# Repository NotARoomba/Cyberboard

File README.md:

<h1 align="center">
  <br>
  
  <br>
  Cyberboard V2
  <br>
</h1>

<h4 align="center">
A Raspberry Pi Pico-sized STM32 development board with Bluetooth, battery support, IMU and a barometer!
</h4>

<div align="center">

</div>

<p align="center">
  <a href="#key-features">Key Features</a> •
  <a href="#pcb">PCB</a> •
  <a href="#credits">Credits</a> •
  <a href="#license">License</a>
</p>

> **⚠️ Looking for V1?** The first version of the Cyberboard is available in the [v1 branch](https://github.com/notaroomba/cyberboard/tree/v1), but be warned: it doesn't work. V2 is a complete redesign with proper functionality.

## Key Features

- **STM32WB55CG** microcontroller with Bluetooth support
- **Raspberry Pi Pico form factor** for compatibility
- **IMU and Barometer** - ICM-42688 (6-axis) and BMP580 pressure sensor for environmental/motion sensing
- **Battery charging** with BQ24072RGTR IC and solder pad for 1S LiPo
- **Buck-Boost converter** (TPS631000) for efficient power management
- **Multiple Status LEDs** for visual feedback
- **USB-C** connectivity
- **Ceramic Bluetooth antenna** with impedance matching
- **SWD test points** on the bottom for easy programming
- **4-layer PCB** design with optimized RF layout and routing
- **Panelized design** for cost-effective manufacturing

## PCB

Designed in KiCad with attention to RF design, power management, and sensor integration. The board features a 4-layer stackup (SIG/GND/PWR/SIG) with optimized routing for the Bluetooth antenna and sensitive analog signals.

### Schematic

### PCB Layers

The 4-layer stackup (SIG/GND/PWR/SIG) provides optimal signal integrity and power distribution:

**Layer 1 (Signal):**

**Layer 2 (Ground):**

**Layer 3 (Power):**

**Layer 4 (Signal):**

**Front:**

**Back:**

### JLCPCB Order

## Credits

This project uses:

- [KiCad](https://www.kicad.org/)
- [Blender](https://www.blender.org/) for 3D renders
- [Hack Club Blueprint](https://blueprint.hackclub.com/projects/491)

## You may also like...

- [CyberCard](https://github.com/NotARoomba/CyberCard) – A Cyberpunk themed NFC hacker card
- [Ember](https://github.com/NotARoomba/ember) – USB-C PD Powered Hotplate
- [Trace](https://github.com/NotARoomba/trace) – An ruler for engineers
- [Athena](https://github.com/NotARoomba/athena) – A flight controlelr with a triple MCU architecture

## License

MIT

---

> [notaroomba.dev](https://notaroomba.dev) &nbsp;&middot;&nbsp;
> GitHub [@NotARoomba](https://github.com/NotARoomba) &nbsp;&middot;&nbsp;

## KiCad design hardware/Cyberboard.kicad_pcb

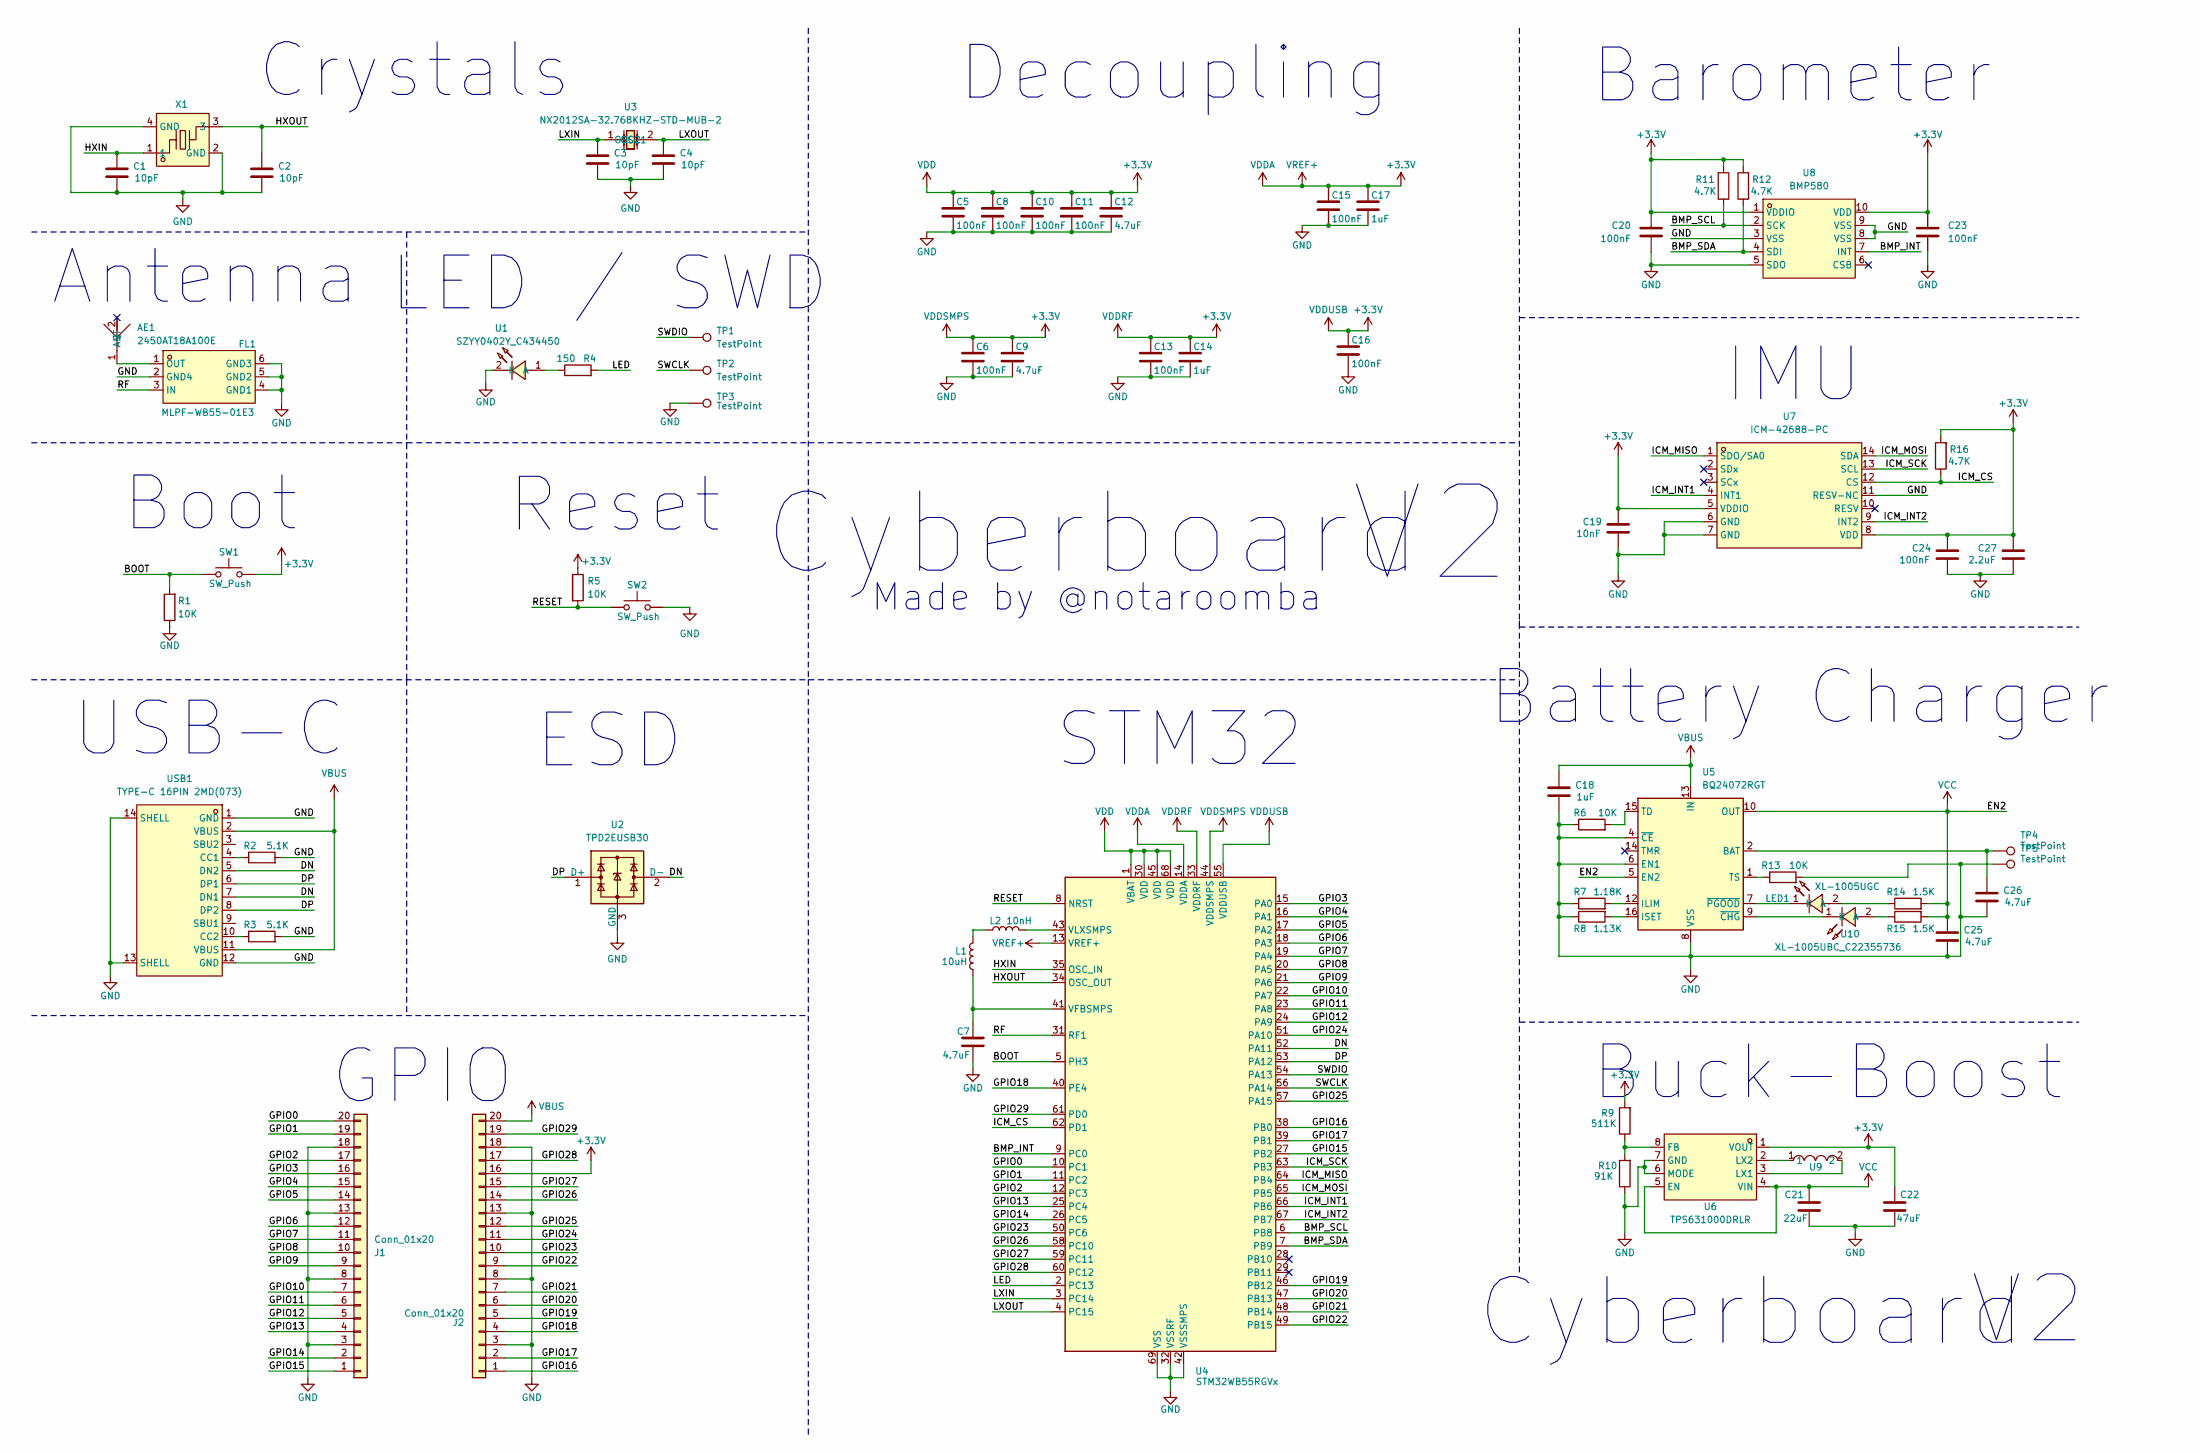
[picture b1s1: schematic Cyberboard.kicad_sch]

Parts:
AE1: 2450AT18A100E; ANT-SMD_L3.2-W1.6; LCSC Part C89334
C1, C2, C3, C4: 10pF; C_0402_1005Metric
C5, C6, C8, C10, C11, C13, C15, C16, C20, C23, C24: 100nF; C_0402_1005Metric
C7, C9, C12, C25, C26: 4.7uF; C_0603_1608Metric
C14, C17, C18: 1uF; C_0402_1005Metric
C19: 10nF; C_0402_1005Metric
C21: 22uF; C_0603_1608Metric; LCSC C361061
C22: 47uF; C_0805_2012Metric; LCSC C471380
C27: 2.2uF; C_0402_1005Metric
FL1: MLPF-WB55-01E3; FILTER-SMD_6P-L1.6-W1.0-P0.50-BL; LCSC Part C2651048
J1, J2: Conn_01x20; PinHeader_1x20_P2.54mm_Vertical; LCSC C42431804
L1: 10uH; L_0603_1608Metric
L2: 10nH; L_0603_1608Metric
LED1: XL-1005UGC; LED0402-RD_GREEN; LCSC Part C965793
R1, R5, R6, R13: 10K; R_0402_1005Metric
R2, R3: 5.1K; R_0402_1005Metric
R4: 150; R_0402_1005Metric; LCSC C25082
R7: 1.18K; R_0402_1005Metric
R8: 1.13K; R_0402_1005Metric
R9: 511K; R_0402_1005Metric
R10: 91K; R_0402_1005Metric
R11, R12, R16: 4.7K; R_0402_1005Metric
R14, R15: 1.5K; R_0402_1005Metric
SW1, SW2: SW_Push; SW-SMD_L3.9-W3.0-P4.45; LCSC C720477
TP1, TP2, TP3: TestPoint; TestPoint_Pad_1.0x1.0mm
TP4, TP5: TestPoint; TestPoint_Pad_2.0x2.0mm
U1: SZYY0402Y_C434450; LED0402-FD_YELLOW; LCSC Part C434450
U2: TPD2EUSB30; Texas_DRT-3
U3: NX2012SA-32.768KHZ-STD-MUB-2; CRYSTAL-SMD_L2.0-W1.2; LCSC Part C891748
U4: STM32WB55RGVx; QFN-68-1EP_8x8mm_P0.4mm_EP6.4x6.4mm; LCSC C401505
U5: BQ24072RGT; VQFN-16-1EP_3x3mm_P0.5mm_EP1.6x1.6mm; LCSC C140288
U6: TPS631000DRLR; SOT-583-8_L2.1-W1.2-P0.50-LS1.6-BL; LCSC Part C5219190
U7: ICM-42688-PC; LGA-14_L3.0-W2.5-P0.50-TL; LCSC Part C48586483
U8: BMP580; LGA-10_L2.0-W2.0-P0.50-TL_BMP580; LCSC Part C22391138
U9: DFE252012P-1R0M=P2; L1008; LCSC Part C882955
U10: XL-1005UBC_C22355736; LED0402-RD; LCSC Part C22355736
USB1: TYPE-C 16PIN 2MD(073); USB-C-SMD_TYPE-C-6PIN-2MD-073; LCSC Part C2765186
X1: NX2016SA-32MHZ-STD-CZS-5; OSC-SMD_4P-L2.0-W1.6-BL; LCSC Part C843260

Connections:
+3.3V: C5.1, C6.1, C8.1, C9.1, C10.1, C11.1, C12.1, C13.1, C14.1, C15.1, C16.1, C17.1, C19.1, C20.1, C22.1, C23.1, C24.1, C27.1, J2.16, R5.1, R9.2, R11.2, R12.2, R16.2, SW1.2, U4.1 (VBAT), U4.13 (VREF+), U4.14 (VDDA), U4.30 (VDD), U4.33 (VDDRF), U4.44 (VDDSMPS), U4.45 (VDD), U4.55 (VDDUSB), U4.68 (VDD), U6.1 (VOUT), U7.5 (VDDIO), U7.8 (VDD), U8.1 (VDDIO), U8.10 (VDD)
/BMP_INT: U4.9 (PC0), U8.7 (INT)
/BMP_SCL: R11.1, U4.6 (PB8), U8.2 (SCK)
/BMP_SDA: R12.1, U4.7 (PB9), U8.4 (SDI)
/BOOT: R1.2, SW1.1, U4.5 (PH3)
/DN: U2.2 (D-), U4.52 (PA11), USB1.5 (DN2), USB1.7 (DN1)
/DP: U2.1 (D+), U4.53 (PA12), USB1.6 (DP1), USB1.8 (DP2)
/GPIO0: J1.20, U4.10 (PC1)
/GPIO1: J1.19, U4.11 (PC2)
/GPIO2: J1.17, U4.12 (PC3)
/GPIO3: J1.16, U4.15 (PA0)
/GPIO4: J1.15, U4.16 (PA1)
/GPIO5: J1.14, U4.17 (PA2)
/GPIO6: J1.12, U4.18 (PA3)
/GPIO7: J1.11, U4.19 (PA4)
/GPIO8: J1.10, U4.20 (PA5)
/GPIO9: J1.9, U4.21 (PA6)
/GPIO10: J1.7, U4.22 (PA7)
/GPIO11: J1.6, U4.23 (PA8)
/GPIO12: J1.5, U4.24 (PA9)
/GPIO13: J1.4, U4.25 (PC4)
/GPIO14: J1.2, U4.26 (PC5)
/GPIO15: J1.1, U4.27 (PB2)
/GPIO16: J2.1, U4.38 (PB0)
/GPIO17: J2.2, U4.39 (PB1)
/GPIO18: J2.4, U4.40 (PE4)
/GPIO19: J2.5, U4.46 (PB12)
/GPIO20: J2.6, U4.47 (PB13)
/GPIO21: J2.7, U4.48 (PB14)
/GPIO22: J2.9, U4.49 (PB15)
/GPIO23: J2.10, U4.50 (PC6)
/GPIO24: J2.11, U4.51 (PA10)
/GPIO25: J2.12, U4.57 (PA15)
/GPIO26: J2.14, U4.58 (PC10)
/GPIO27: J2.15, U4.59 (PC11)
/GPIO28: J2.17, U4.60 (PC12)
/GPIO29: J2.19, U4.61 (PD0)
/HXIN: C1.1, U4.35 (OSC_IN), X1.1
/HXOUT: C2.1, U4.34 (OSC_OUT), X1.3
/ICM_CS: R16.1, U4.62 (PD1), U7.12 (CS)
/ICM_INT1: U4.66 (PB6), U7.4 (INT1)
/ICM_INT2: U4.67 (PB7), U7.9 (INT2)
/ICM_MISO: U4.64 (PB4), U7.1 (SDO/SA0)
/ICM_MOSI: U4.65 (PB5), U7.14 (SDA)
/ICM_SCK: U4.63 (PB3), U7.13 (SCL)
/LED: R4.2, U4.2 (PC13)
/LXIN: C3.1, U3.1 (OSC1), U4.3 (PC14)
/LXOUT: C4.1, U3.2 (OSC2), U4.4 (PC15)
/RESET: R5.2, SW2.1, U4.8 (NRST)
/RF: FL1.3 (IN), U4.31 (RF1)
/SWCLK: TP2.1, U4.56 (PA14)
/SWDIO: TP1.1, U4.54 (PA13)
GND: C1.2, C2.2, C3.2, C4.2, C5.2, C6.2, C7.2, C8.2, C9.2, C10.2, C11.2, C12.2, C13.2, C14.2, C15.2, C16.2, C17.2, C18.2, C19.2, C20.2, C21.2, C22.2, C23.2, C24.2, C25.2, C26.2, C27.2, FL1.2 (GND4), FL1.4 (GND1), FL1.5 (GND2), FL1.6 (GND3), J1.3, J1.8, J1.13, J1.18, J2.3, J2.8, J2.13, J2.18, R1.1, R2.2, R3.2, R6.1, R7.1, R8.1, R10.1, R13.2, SW2.2, TP3.1, TP5.1, U1.2 (K), U2.3 (GND), U4.32 (VSSRF), U4.42 (VSSSMPS), U4.69 (VSS), U5.4 (~CE), U5.6 (EN1), U5.8 (VSS), U5.17 (VSS), U6.6 (MODE), U6.7 (GND), U7.6 (GND), U7.7 (GND), U7.11 (RESV-NC), U8.3 (VSS), U8.5 (SDO), U8.8 (VSS), U8.9 (VSS), USB1.1 (GND), USB1.12 (GND), USB1.13 (SHELL), USB1.14 (SHELL), X1.2 (GND), X1.4 (GND)
unnamed: AE1.1 (ANT), FL1.1 (OUT)
unnamed: C26.1, TP4.1, U5.2 (BAT), U5.3 (BAT)
unnamed: L1.1, L2.2
unnamed: LED1.2 (A), R14.1
unnamed: LED1.1 (K), U5.7 (~PGOOD)
unnamed: R4.1, U1.1 (A)
unnamed: C7.1, L1.2, U4.41 (VFBSMPS)
unnamed: L2.1, U4.43 (VLXSMPS)
unnamed: R7.2, U5.12 (ILIM)
unnamed: R8.2, U5.16 (ISET)
unnamed: R6.2, U5.15 (TD)
unnamed: R13.1, U5.1 (TS)
unnamed: R9.1, R10.2, U6.8 (FB)
unnamed: U6.3 (LX1), U9.2
unnamed: U6.2 (LX2), U9.1
unnamed: R15.1, U10.2 (A)
unnamed: U5.9 (~CHG), U10.1 (K)
unnamed: R2.1, USB1.4 (CC1)
unnamed: R3.1, USB1.10 (CC2)
VBUS: C18.1, J2.20, U5.13 (IN), USB1.2 (VBUS), USB1.11 (VBUS)
VCC: C21.1, C25.1, R14.2, R15.2, U5.5 (EN2), U5.10 (OUT), U5.11 (OUT), U6.4 (VIN), U6.5 (EN)

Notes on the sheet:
Cyberboard
Decoupling
IMU
Made by @notaroomba
Reset
LED / SWD
Antenna
STM32
ESD
Battery Charger
Boot
USB-C
Buck-Boost
Barometer
GPIO
Crystals

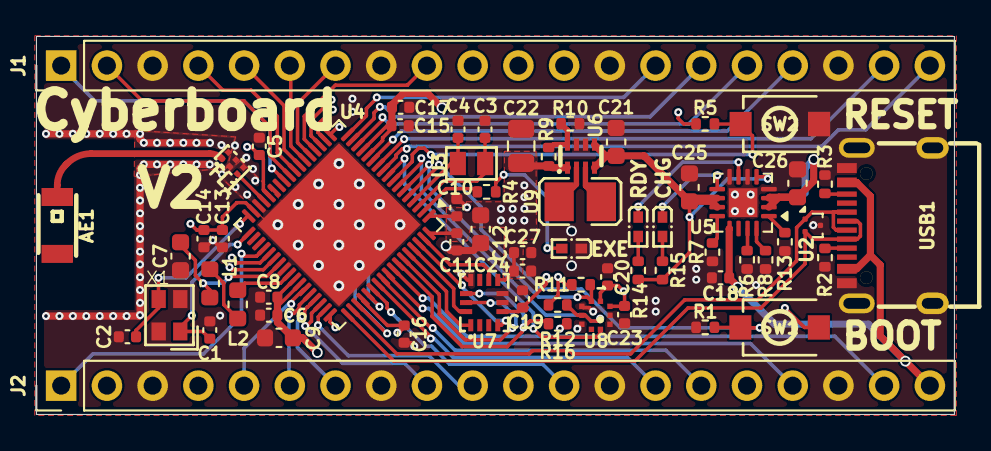
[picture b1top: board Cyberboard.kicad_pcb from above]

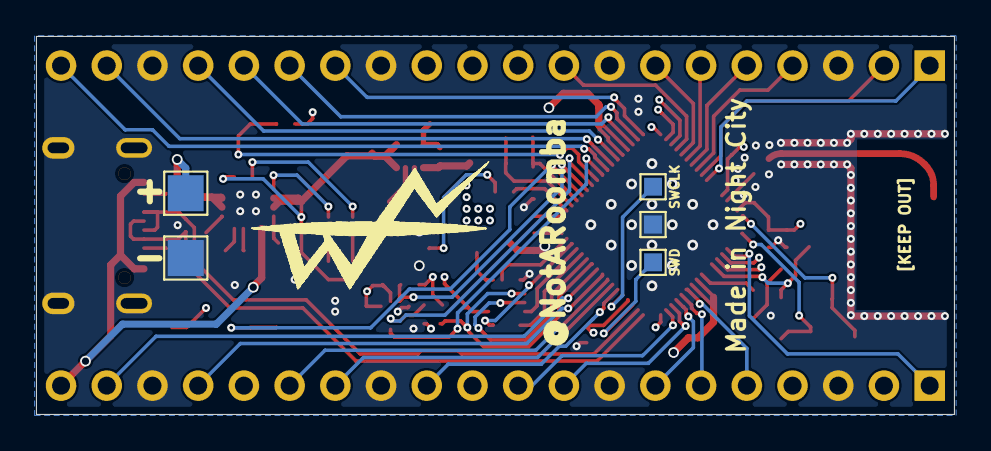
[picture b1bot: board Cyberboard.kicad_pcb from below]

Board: 4 copper layers, 51.0 x 21.0 mm, 69 parts (5 on the bottom side), 74 nets.

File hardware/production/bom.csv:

Designator,Footprint,Quantity,Value,LCSC Part #
AE1,ANT-SMD_L3.2-W1.6,1,2450AT18A100E,C89334
"C1, C2, C3, C4",0402,4,10pF,
"C10, C11, C13, C15, C16, C20, C23, C24, C5, C6, C8",0402,11,100nF,
"C12, C25, C26, C7, C9",0603,5,4.7uF,
"C14, C17, C18",0402,3,1uF,
C19,0402,1,10nF,
C21,0603,1,22uF,C361061
C22,0805,1,47uF,C471380
C27,0402,1,2.2uF,
FL1,FILTER-SMD_6P-L1.6-W1.0-P0.50-BL,1,MLPF-WB55-01E3,C2651048
"J1, J2",PinHeader_1x20_P2.54mm_Vertical,2,Conn_01x20,C42431804
L1,0603,1,10uH,
L2,0603,1,10nH,
LED1,LED0402-RD_GREEN,1,XL-1005UGC,C965793
"R1, R13, R5, R6",0402,4,10K,
R10,0402,1,91K,
"R11, R12, R16",0402,3,4.7K,
"R14, R15",0402,2,1.5K,
"R2, R3",0402,2,5.1K,
R4,0402,1,150,C25082
R7,0402,1,1.18K,
R8,0402,1,1.13K,
R9,0402,1,511K,
"SW1, SW2",SW-SMD_L3.9-W3.0-P4.45,2,SW_Push,C720477
U1,LED0402-FD_YELLOW,1,SZYY0402Y_C434450,C434450
U10,LED0402-RD,1,XL-1005UBC_C22355736,C22355736
U2,Texas_DRT-3,1,TPD2EUSB30,
U3,CRYSTAL-SMD_L2.0-W1.2,1,NX2012SA-32.768KHZ-STD-MUB-2,C891748
U4,QFN-68-1EP_8x8mm_P0.4mm_EP6.4x6.4mm,1,STM32WB55RGVx,C401505
U5,VQFN-16-1EP_3x3mm_P0.5mm_EP1.6x1.6mm,1,BQ24072RGT,C140288
U6,SOT-583-8_L2.1-W1.2-P0.50-LS1.6-BL,1,TPS631000DRLR,C5219190
U7,LGA-14_L3.0-W2.5-P0.50-TL,1,ICM-42688-PC,C48586483
U8,LGA-10_L2.0-W2.0-P0.50-TL_BMP580,1,BMP580,C22391138
U9,L1008,1,DFE252012P-1R0M=P2,C882955
USB1,USB-C-SMD_TYPE-C-6PIN-2MD-073,1,TYPE-C 16PIN 2MD(073),C2765186
X1,OSC-SMD_4P-L2.0-W1.6-BL,1,NX2016SA-32MHZ-STD-CZS-5,C843260

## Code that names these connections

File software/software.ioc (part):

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Mcu.Name=STM32WB55RGVx
Mcu.Package=VFQFPN68
Mcu.UserName=STM32WB55RGVx
PA11.Mode=Device
PA11.Signal=USB_DM
PA12.Mode=Device
PA12.Signal=USB_DP
PB3.GPIOParameters=GPIO_Label
PB3.GPIO_Label=ICM_SCK
PB3.Mode=Full_Duplex_Master
PB3.Signal=SPI1_SCK
PB4.GPIOParameters=GPIO_Label
PB4.GPIO_Label=ICM_MISO
PB4.Mode=Full_Duplex_Master
PB4.Signal=SPI1_MISO
PB5.GPIOParameters=GPIO_Label
PB5.GPIO_Label=ICM_MOSI
PB5.Mode=Full_Duplex_Master
PB5.Signal=SPI1_MOSI
PB6.GPIOParameters=GPIO_Label
PB6.GPIO_Label=ICM_INT1
PB6.Signal=GPXTI6
PB7.GPIOParameters=GPIO_Label
PB7.GPIO_Label=ICM_INT2
PB7.Signal=GPXTI7
PB8.GPIOParameters=GPIO_Label
PB8.GPIO_Label=BMP_SCL
PB8.Mode=I2C
PB8.Signal=I2C1_SCL
PB9.GPIOParameters=GPIO_Label
PB9.GPIO_Label=BMP_SDA
PB9.Mode=I2C
PB9.Signal=I2C1_SDA
PC0.GPIOParameters=GPIO_Label
PC0.GPIO_Label=BMP_INT
PC0.Signal=GPXTI0
PC13.GPIOParameters=PinState,GPIO_PuPd,GPIO_Label
PC13.GPIO_Label=LED
PC13.GPIO_PuPd=GPIO_PULLUP
PC13.PinState=GPIO_PIN_SET
PC13.Signal=GPIO_Output
PC14-OSC32_IN.Mode=LSE-External-Oscillator
PC14-OSC32_IN.Signal=RCC_OSC32_IN
PC15-OSC32_OUT.Mode=LSE-External-Oscillator
PC15-OSC32_OUT.Signal=RCC_OSC32_OUT
PD1.GPIOParameters=GPIO_Speed,PinState,GPIO_Label
PD1.GPIO_Label=ICM_CS
PD1.GPIO_Speed=GPIO_SPEED_FREQ_VERY_HIGH
PD1.PinState=GPIO_PIN_SET
PD1.Signal=GPIO_Output
RCC.HSE_VALUE=32000000
RCC.SYSCLKFreq_VALUE=64000000
RCC.SYSCLKSource=RCC_SYSCLKSOURCE_PLLCLK
board=custom

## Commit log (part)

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2025-10-15 added stuff
2025-10-15 finished layout
2025-10-16 add readme and also blender files
2025-10-16 add order and prod files
2025-10-16 resized keep out
2025-10-16 clip lol
2025-10-17 updated pcb for single side pcba
2025-10-18 Rename section to '3D Renders (Old Layout)'
2025-10-20 prod final
2025-10-21 forgot resistor values and change in inductor footprint
2025-11-12 replaces
2025-11-18 image
2025-12-10 updated image and banner
2025-12-10 Change logo image source in README
    Updated logo image source in README.
2025-12-10 remove old assets
2025-12-11 Update battery charging description in README
2025-12-11 Update README features section wording
2025-12-11 Remove features list from PCB section
    Removed features section from PCB description.
2025-12-11 Update README with PCB layer images
    Added images for PCB layers and front/back views.
2025-12-12 Update project recommendations in README
    Removed outdated project links and added new projects.
2026-03-06 add in firmware
2026-03-07 add imu
2026-03-07 it works
2026-03-08 it works!!
2026-03-08 bluetooth works
2026-03-08 aaaa
2026-03-08 ble stuff
2026-03-08 better filtering
2026-03-08 move around firmware and create websocket server
2026-03-08 better server
2026-03-08 add in build
2026-03-08 Create CNAME
2026-03-08 add in favicon
2026-03-08 mobile optimization
2026-03-09 Create software.code-workspace
2026-03-12 readme upda
2026-04-02 fix corrupted file
